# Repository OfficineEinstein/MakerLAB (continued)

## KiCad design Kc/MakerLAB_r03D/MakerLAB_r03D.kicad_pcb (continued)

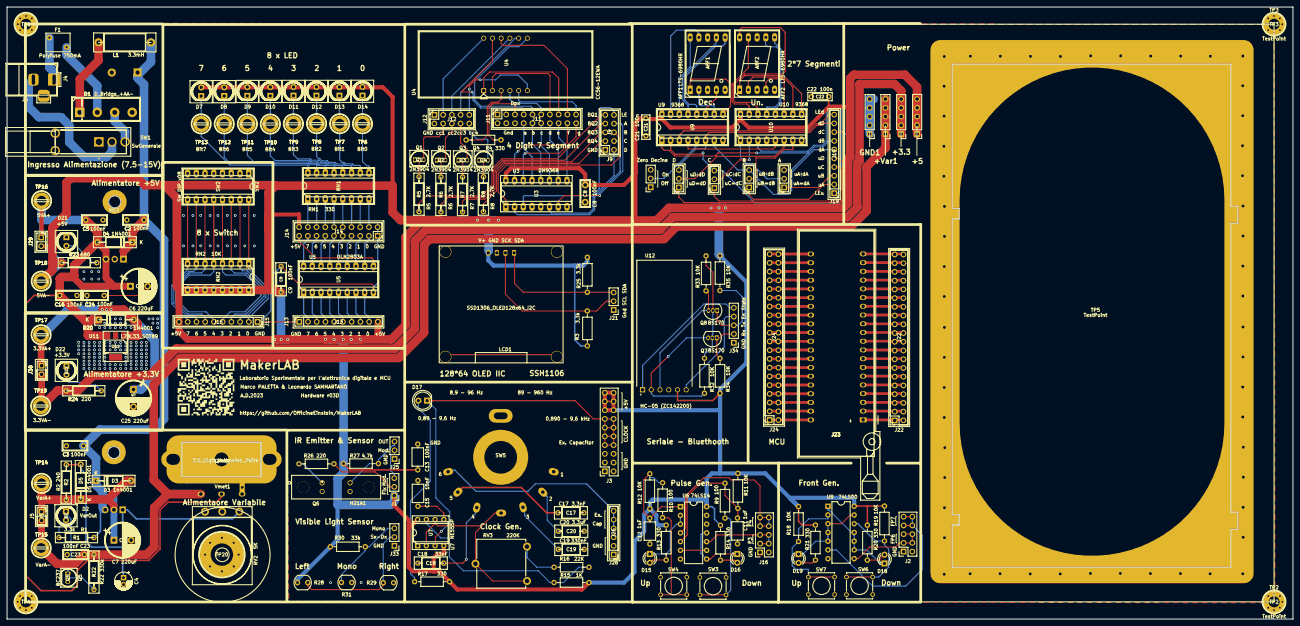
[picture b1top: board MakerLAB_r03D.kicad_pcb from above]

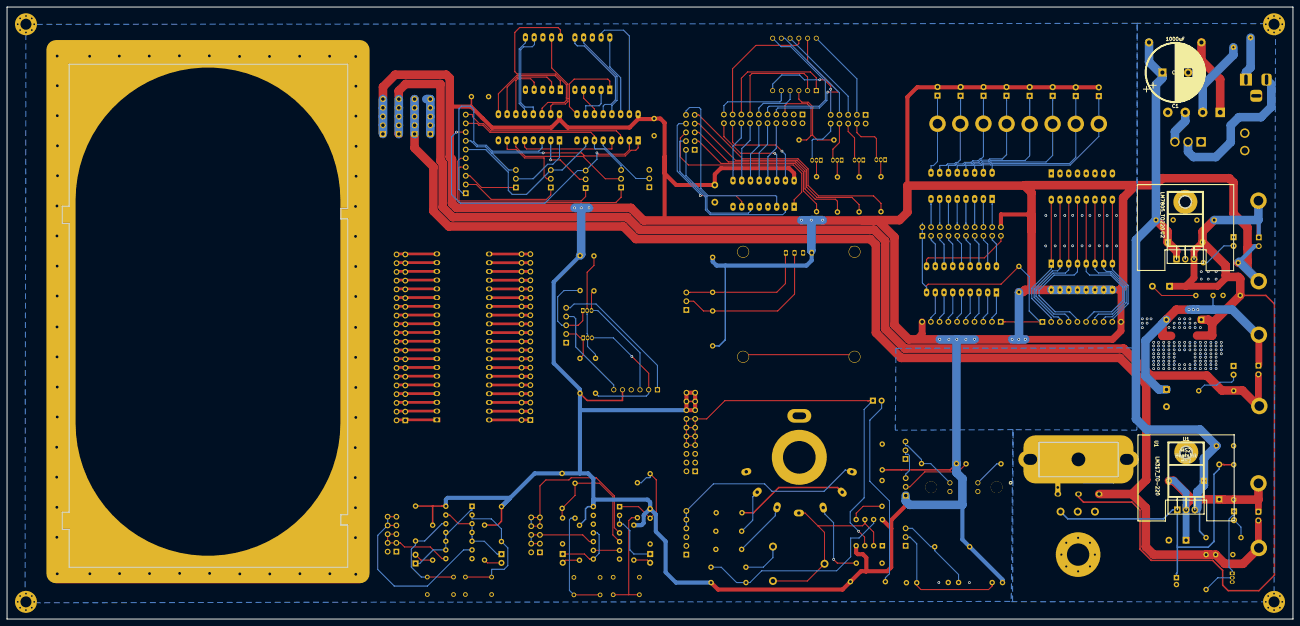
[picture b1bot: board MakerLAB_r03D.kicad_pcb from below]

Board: 2 copper layers, 374.0 x 178.0 mm, 183 parts (5 on the bottom side), 212 nets.

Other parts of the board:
J2: FP6 FP7; PinSocket_2x05_P2.54mm_Vertical
Q7, Q8: BS170; TO-92_Inline
R34, R35: 10K; R_Axial_DIN0207_L6.3mm_D2.5mm_P10.16mm_Horizontal

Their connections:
/Alimentazione/+5V: R34.2, R35.2; also elsewhere on the board
unnamed 61: J2.3, J2.4, J2.5, J2.6; also elsewhere on the board
unnamed 62: J2.7, J2.8, J2.9, J2.10; also elsewhere on the board
unnamed 193: Q7.3 (S); also elsewhere on the board
unnamed 194: Q8.3 (S); also elsewhere on the board

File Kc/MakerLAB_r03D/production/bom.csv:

Designator,Footprint,Quantity,Value,LCSC Part #
"+3.3, +5, +Var1, GND1, J34",PinHeader_1x05_P2.54mm_Vertical,5,Conn_01x05,
"AFF1, AFF2",7SegmentLED_LTS6760_LTS6780,2,LTS-6980HR,
C1,CP_Radial_D17.0mm_P7.50mm,1,1000uF,
"C11, C12",C_Axial_L5.1mm_D3.1mm_P7.50mm_Horizontal,2,1uF,
C13,C_Axial_L5.1mm_D3.1mm_P7.50mm_Horizontal,1,100nF,
C15,C_Axial_L5.1mm_D3.1mm_P7.50mm_Horizontal,1,10nF,
"C16, C2, C23, C24, C3, C5",C_Disc_D7.0mm_W2.5mm_P5.00mm,6,100nF,
C17,C_Axial_L5.1mm_D3.1mm_P7.50mm_Horizontal,1,"3,3nF",
C18,C_Axial_L5.1mm_D3.1mm_P7.50mm_Horizontal,1,33nF,
C19,C_Axial_L5.1mm_D3.1mm_P7.50mm_Horizontal,1,330nF,
C20,C_Axial_L5.1mm_D3.1mm_P7.50mm_Horizontal,1,"3,3uF",
"C21, C22",C_Disc_D4.3mm_W1.9mm_P5.00mm,2,100n,
"C25, C6, C7",CP_Radial_D10.0mm_P5.00mm,3,220uF,
C4,CP_Radial_D5.0mm_P2.00mm,1,10uF,
C8,C_Disc_D7.5mm_W2.5mm_P5.00mm,1,100nF,
C9,C_Axial_L3.8mm_D2.6mm_P7.50mm_Horizontal,1,100nF,
D1,Diode_Bridge_Vishay_KBL,1,D_Bridge_+AA-,
D10,LED_D5.0mm,1,4,
D11,LED_D5.0mm,1,3,
D12,LED_D5.0mm,1,2,
D13,LED_D5.0mm,1,1,
D14,LED_D5.0mm,1,0,
"D15, D16, D18, D19",LED_D3.0mm,4,LED,
D17,LED_D5.0mm,1,LED,
D2,LED_D5.0mm,1,VarOut,
"D20, D3, D4, D5",D_A-405_P10.16mm_Horizontal,4,1N4001,
D21,LED_D5.0mm,1,+5V,
D22,LED_D5.0mm,1,+3.3V,
D7,LED_D5.0mm,1,7,
D8,LED_D5.0mm,1,6,
D9,LED_D5.0mm,1,5,
F1,RV_Disc_D7mm_W5.4mm_P5mm,1,Polyfuse 750mA,
"HS1, HS2",Heatsink_28x25_Horiz,2,Heatsink,
J1,PinHeader_1x03_P2.54mm_Vertical,1,Fix-Mod,
"J11, J3",PinSocket_2x10_P2.54mm_Vertical,2,Conn_02x10_Counter_Clockwise,
"J12, J16, J2, J9",PinSocket_2x05_P2.54mm_Vertical,4,Conn_02x05_Counter_Clockwise,
J13,PinSocket_1x10_P2.54mm_Vertical,1,GND 0  1  2  3  4  5  6  7  +5V,
J14,PinSocket_2x10_P2.54mm_Vertical,1,8Bit Jumper,
J15,PinSocket_1x10_P2.54mm_Vertical,1,GND 0  1  2  3  4  5  6  7 +5V,
J19,PinHeader_1x10_P2.54mm_Vertical,1,Conn_01x10_Female,
J21,PinHeader_1x03_P2.54mm_Vertical,1,Conn_01x03,
"J22, J24",PinSocket_2x20_P2.54mm_Vertical,2,Conn_02x20_Counter_Clockwise,
J23,DIP_Socket-40_W22.1_W22.86_W25.4_W27.94_W28.7_3M_240-3639-00-0602J,1,Conn_02x20_Counter_Clockwise,
J25,PinHeader_1x03_P2.54mm_Vertical,1,IR Emitter & Sensor,
J26,PinHeader_1x06_P2.54mm_Vertical,1,Conn_01x06_Female,
"J29, J30, J5",PinSocket_1x02_P2.54mm_Vertical,3,Conn_01x02_Male,
J33,PinHeader_1x03_P2.54mm_Vertical,1,Visible Light Sensor,
J4,BarrelJack_Horizontal,1,Barrel_Jack_MountingPin,
L1,L_Axial_L12.0mm_D5.0mm_P15.24mm_Horizontal_Fastron_MISC,1,"3,3mH",
LCD1,TFT OLED 1.3 I2C,1,SSD1306_OLED128x64_I2C,
"Q1, Q2, Q3, Q4",TO-92_Inline,4,2N3904,
Q5,TO-92_Inline,1,BC237,
Q6,H21A1,1,H21A1,
"Q7, Q8",TO-92_Inline,2,BS170,
"R1, R25, R3",R_Axial_DIN0207_L6.3mm_D2.5mm_P10.16mm_Horizontal,3,"3,3k",
"R10, R9",R_Axial_DIN0207_L6.3mm_D2.5mm_P10.16mm_Horizontal,2,100,
"R11, R12, R18, R19, R32, R33, R34, R35",R_Axial_DIN0207_L6.3mm_D2.5mm_P10.16mm_Horizontal,8,10K,
"R13, R14, R17, R20, R21, R4",R_Axial_DIN0207_L6.3mm_D2.5mm_P10.16mm_Horizontal,6,330,
R15,R_Axial_DIN0207_L6.3mm_D2.5mm_P10.16mm_Horizontal,1,1K,
R16,R_Axial_DIN0207_L6.3mm_D2.5mm_P10.16mm_Horizontal,1,22K,
R2,R_Axial_DIN0207_L6.3mm_D2.5mm_P10.16mm_Horizontal,1,240,
R22,R_Axial_DIN0207_L6.3mm_D2.5mm_P10.16mm_Horizontal,1,330k,
R23,R_Axial_DIN0207_L6.3mm_D2.5mm_P10.16mm_Horizontal,1,680,
"R24, R26",R_Axial_DIN0207_L6.3mm_D2.5mm_P10.16mm_Horizontal,2,220,
R27,R_Axial_DIN0207_L6.3mm_D2.5mm_P10.16mm_Horizontal,1,"4,7k",
R28,R_LDR_5.0x4.1mm_P3mm_Vertical,1,Left,
R29,R_LDR_5.0x4.1mm_P3mm_Vertical,1,Right,
R30,R_Axial_DIN0207_L6.3mm_D2.5mm_P10.16mm_Horizontal,1,33k,
R31,R_LDR_5.0x4.1mm_P3mm_Vertical,1,Mono,
"R5, R6, R7, R8",R_Axial_DIN0207_L6.3mm_D2.5mm_P10.16mm_Horizontal,4,R,
RN1,DIP-16_W7.62mm_Socket_LongPads,1,Resistor Array,
RN2,DIP-16_W7.62mm_Socket_LongPads,1,10K,
RV2,Potentiometer_Omeg_PC16BU_Vertical,1,5K,
RV3,Potentiometer_ACP_CA14V-15_Vertical,1,220K,
SW1,SW_100SP1T2B4M7QE,1,SwGenerale,
SW2,DIP-16_W7.62mm_Socket_LongPads,1,SW_DIP_x08,
"SW3, SW4, SW6, SW7",SW_Tactile_Straight_KSL0Axx1LFTR,4,SW_Push,
SW5,Commutatore 2x6,1,SW_Rotary12,
"TP1, TP2, TP3, TP4",MountingHole_3.2mm_M3_Pad_Via,4,TestPoint,
TP10,TestPoint_Loop_D3.80mm_Drill2.8mm,1,Bit4,
TP11,TestPoint_Loop_D3.80mm_Drill2.8mm,1,Bit5,
TP12,TestPoint_Loop_D3.80mm_Drill2.8mm,1,Bit6,
TP13,TestPoint_Loop_D3.80mm_Drill2.8mm,1,Bit7,
TP14,TestPoint_Loop_D3.80mm_Drill2.8mm,1,VarA+,
TP15,TestPoint_Loop_D3.80mm_Drill2.8mm,1,VarA-,
TP16,TestPoint_Loop_D3.80mm_Drill2.8mm,1,5VA+,
TP17,TestPoint_Loop_D3.80mm_Drill2.8mm,1,3.3VA+,
TP18,TestPoint_Loop_D3.80mm_Drill2.8mm,1,5VA-,
TP19,TestPoint_Loop_D3.80mm_Drill2.8mm,1,3.3VA-,
TP20,MountingHole_6.5mm_Pad_Via,1,Potenziometer,
TP21,Alimentatore Variabile,1,Alimentaore Variabile,
TP22,Alimentatore Variabile,1,"Alimentatore +3,3V",
TP23,Alimentatore Variabile,1,Alimentatore +5V,
TP24,Alimentatore Variabile,1,"Ingresso Alimentazione (7,5-15V)",
TP25,Alimentatore Variabile,1,8 x Switch,
TP26,Alimentatore Variabile,1,8 x LED,
TP27,Disp4x7Seg,1,8 x LED,
TP28,MakerLABTitoli,1,MakerLAB,
TP29,Clock NE555,1,8 x LED,
"TP31, TP35",Disp4x7Seg,2,Pulse Generator,
TP32,Disp4x7Seg,1,BT to Serial,
TP34,Disp4x7Seg,1,2 Digit 7 Seg,
TP5,BreadBoard 81x146,1,TestPoint,
TP6,TestPoint_Loop_D3.80mm_Drill2.8mm,1,Bit0,
TP7,TestPoint_Loop_D3.80mm_Drill2.8mm,1,Bit1,
TP8,TestPoint_Loop_D3.80mm_Drill2.8mm,1,Bit2,
TP9,TestPoint_Loop_D3.80mm_Drill2.8mm,1,Bit3,
U1,TO-220-3_Horizontal_TabDown,1,LM317_TO-220,
"U10, U9",DIP-16_W7.62mm_Socket_LongPads,2,9368,
U11,SOT-223,1,L78L33_SOT89,
U12,HC-05 Module Horizontal (ZC14200),1,HC-05 (ZC142200),
U2,TO-220-3_Horizontal_TabDown,1,LM7805_TO220,
U3,DIP-16_W7.62mm_LongPads,1,DM9368,
U4,CA56-12EWA,1,CC56-12EWA,
U5,DIP-18_W7.62mm_Socket_LongPads,1,ULN2803A,
U6,DIP-14_W7.62mm,1,74LS14,
U7,DIP-8_W7.62mm,1,NE555P,
U8,DIP-14_W7.62mm,1,74LS00,
"Uni-A0, Uni-A1, Uni-A2, Uni-A3, Uni-A4",PinSocket_1x03_P2.54mm_Vertical,5,Jumper_3_Open,
Vmet1,"3,5 Digit 0,28'' Voltmeter",1,"3,5_Digit_Voltmeter_3Wire",

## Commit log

2023-03-09 PuntoZero
2023-03-09 20230309-Update
    Lavoro in tandem con Marco
2023-03-15 Power Unit
    Iniziato a sistemare l'unità alimentatore
2023-03-16 Power Supply
    Seconda fase
2023-03-20 Layout Alimentatori OK
2023-03-20 Bozza con LCD 16x2
2023-03-21 test Ma<rco
2023-03-21 Up a Scuola del 21
2023-03-27 inizio lavoro 20230327
2023-03-27 27 notte
2023-03-28 20230328-13
    20230328-13
2023-03-28 Born r03B
2023-03-28 sbroglio pulser e fronti
2023-03-28 versione r03B della notte del 28 marzo 2023
2023-03-28 Aggiornamento Foto di copertina
2023-03-28 e la foto di copertina ridimensionata
2023-03-31 r03C
2023-04-03 20230403 - Routing in corso
2023-04-03 20230403 17:12
2023-04-04 20230404 2:20
2023-04-04 20230404 14:30
2023-04-04 Routing e Zone OK
2023-04-04 test schematic scritte
2023-04-04 visual 4 dgt scritte
2023-04-04 4 DGT SCRITTE 2
2023-04-04 Up Serigrafie
2023-04-05 SCHEMI CONN ANNOTATI
    CONNETTORI ANNOTATI 5.4.23
2023-04-20 Sub r03D
    Subver per completamento grafica del PCB
2023-04-21 Versione D prima del controllo di fine sessione
2023-04-21 Fine Controllo
2023-04-21 Pannello frontale
    MakerLAB r03D
2023-04-21 Update README.md
    pannello dello strumento r03D
2023-04-27 Ultima prima del logo
2023-04-27 Con Supporto Breadboard
2023-04-27 Versione finale, aprile 2023
    Demo Board in produzione.
2023-04-27 28-4-2023
    Demo Board in produzione
2023-06-27 Add files via upload
    Il MakerLAB operativo
